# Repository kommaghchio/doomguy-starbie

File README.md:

# README

This project is a modified version of Starbie, the week 1 project for the Half-Life competition. This project includes
all the default features of Starbie, except this time with a rechargable battery and a joystick for additional interactivity.

It also bears the shape of a floppy disk, instead of a star, and has a different pet than the default "Sparkle".

I made this for week 1 on the Half-Life Hack Club competition, using KiCad.

Bill Of Materials (BOM):
|Item                            |Qty|Supplier    |Cost/item|Total Cost|link                                                                                                                                                                                                                                                                                                                                                                                                                                                                                                                                                                                                                                                                                                                                         |
|--------------------------------|---|------------|---------|----------|---------------------------------------------------------------------------------------------------------------------------------------------------------------------------------------------------------------------------------------------------------------------------------------------------------------------------------------------------------------------------------------------------------------------------------------------------------------------------------------------------------------------------------------------------------------------------------------------------------------------------------------------------------------------------------------------------------------------------------------------|
|ESP32-C3                        |1  |Seeed Studio|$4.99    |$4.99     |https://www.seeedstudio.com/Seeed-XIAO-ESP32C3-p-5431.html?gad_source=1&gad_campaignid=12740071602&gclid=CjwKCAjw56zWBhB0EiwAdPOQOaJsaVt_9sGyS2N4amANprfpcpzC4ZFOF3GNRDUXlC3SOKTiNB7X-xoCFh8QAvD_BwE                                                                                                                                                                                                                                                                                                                                                                                                                                                                                                                                         |
|Cherry MX switch                |2  |DigiKey     |$0.95    |$1.90     |https://www.digikey.com/en/products/detail/adafruit-industries-llc/5123/14617350?gclsrc=aw.ds&gad_source=1&gad_campaignid=20243136172&gclid=CjwKCAjw56zWBhB0EiwAdPOQOcEKO_ZuNKcFmKH-LIFbnNIoh5SjWSLckSLV59Q7yF32ZynxiMNdxRoC6DoQAvD_BwE                                                                                                                                                                                                                                                                                                                                                                                                                                                                                                      |
|OLED 128 x 64                   |1  |AliExpress  |$2.25    |$2.25     |https://www.aliexpress.us/item/3256808426200900.html?src=google&src=google&albch=shopping&acnt=708-803-3821&isdl=y&slnk=&plac=&mtctp=&albbt=Google_7_shopping&aff_platform=google&aff_short_key=UneMJZVf&gclsrc=aw.ds&albagn=888888&ds_e_adid=&ds_e_matchtype=&ds_e_device=c&ds_e_network=x&ds_e_product_group_id=&ds_e_product_id=en3256808426200900&ds_e_product_merchant_id=5480922393&ds_e_product_country=US&ds_e_product_language=en&ds_e_product_channel=online&ds_e_product_store_id=&ds_url_v=2&albcp=19558607238&albag=&isSmbAutoCall=false&needSmbHouyi=false&gad_source=4&gad_campaignid=19566915268&gclid=CjwKCAjw56zWBhB0EiwAdPOQOWbCcI1XUyzg5GVxmGdN2MzNH9N6fAxHaXDbBD9-6z0KlFHybVR16RoC3KIQAvD_BwE&gatewayAdapt=glo2usa      |
|DHT 11 Sensor                   |1  |AliExpress  |$2.96    |$2.96     |https://www.aliexpress.us/item/3256808886855570.html?src=google&src=google&albch=shopping&acnt=708-803-3821&isdl=y&slnk=&plac=&mtctp=&albbt=Google_7_shopping&aff_platform=google&aff_short_key=UneMJZVf&gclsrc=aw.ds&albagn=888888&ds_e_adid=&ds_e_matchtype=&ds_e_device=c&ds_e_network=x&ds_e_product_group_id=&ds_e_product_id=en3256808886855570&ds_e_product_merchant_id=689344744&ds_e_product_country=US&ds_e_product_language=en&ds_e_product_channel=online&ds_e_product_store_id=&ds_url_v=2&albcp=19558607238&albag=&isSmbAutoCall=false&needSmbHouyi=false&gad_source=4&gad_campaignid=19566915268&gclid=CjwKCAjw56zWBhB0EiwAdPOQOTi8rHT-l1dalaiymuhlZJ_5rcoiuZagXKZtVVNJyw6yZ1U5YU5x8hoCEt0QAvD_BwE&gatewayAdapt=glo2usa       |
|MPU6050                         |1  |AliExpress  |$1.06    |$1.06     |https://www.aliexpress.us/item/3256811811719256.html?src=google&gatewayAdapt=glo2usa                                                                                                                                                                                                                                                                                                                                                                                                                                                                                                                                                                                                                                                         |
|JST S2B-PH-SM4-TB Male connector|1  |DigiKey     |$0.12    |$0.12     |https://www.digikey.com/en/products/detail/jst-sales-america-inc/S2B-PH-SM4-TB/926655                                                                                                                                                                                                                                                                                                                                                                                                                                                                                                                                                                                                                                                        |
|Li-Po Battery                   |1  |DigiKey     |$7.95    |$7.95     |https://www.digikey.com/en/products/detail/pkcell/LP503035-W-PLUG/26906441?gclsrc=aw.ds&gad_source=1&gad_campaignid=23033451739&gclid=CjwKCAjw56zWBhB0EiwAdPOQOZenrkhbt0bE1SlGZxBGAb4lG4wGcrsO8SRFO7WNs4R7fEYOzQB1sRoCiC4QAvD_BwE                                                                                                                                                                                                                                                                                                                                                                                                                                                                                                            |
|KY-023 joystick                 |1  |AliExpress  |$3.84    |$3.84     |https://www.aliexpress.us/item/3256812405746127.html?src=google&src=google&albch=shopping&acnt=231-612-1468&isdl=y&slnk=&plac=&mtctp=&albbt=Google_7_shopping&aff_platform=google&aff_short_key=_oFgTQeV&gclsrc=aw.ds&albagn=888888&ds_e_adid=&ds_e_matchtype=&ds_e_device=c&ds_e_network=x&ds_e_product_group_id=&ds_e_product_id=en3256812405746127&ds_e_product_merchant_id=5703138139&ds_e_product_country=US&ds_e_product_language=en&ds_e_product_channel=online&ds_e_product_store_id=&ds_url_v=2&albcp=23333650963&albag=&isSmbAutoCall=false&needSmbHouyi=false&gad_source=1&gad_campaignid=23324517798&gclid=CjwKCAjw56zWBhB0EiwAdPOQORNeXun5LSGq2G9BXt7lPJ_d5kZQqLntUko0bx6ymKoTvl06xLSpCxoCtxYQAvD_BwE&gatewayAdapt=glo2usa      |
|Male and Female Pin headers     |1  |AliExpress  |$2.12    |$2.12     |https://www.aliexpress.us/item/2255800687544049.html?src=google&snps=y&src=google&albch=shopping&acnt=708-803-3821&isdl=y&slnk=&plac=&mtctp=&albbt=Google_7_shopping&aff_platform=google&aff_short_key=UneMJZVf&gclsrc=aw.ds&albagn=888888&ds_e_adid=&ds_e_matchtype=&ds_e_device=c&ds_e_network=x&ds_e_product_group_id=&ds_e_product_id=en2255800687544049&ds_e_product_merchant_id=107851422&ds_e_product_country=US&ds_e_product_language=en&ds_e_product_channel=online&ds_e_product_store_id=&ds_url_v=2&albcp=20542171667&albag=&isSmbAutoCall=false&needSmbHouyi=false&gad_source=1&gad_campaignid=18545443176&gclid=CjwKCAjw56zWBhB0EiwAdPOQOXWeQ7sWc4y_nkJD0D0cMJH5K3kBbSc2pA1cyd5qMiuMDiqWgesMORoCqAYQAvD_BwE&gatewayAdapt=glo2usa|
|PCB                             |1  |JLCPCB      |$8.99    |$8.99     |https://jlcpcb.com                                                                                                                                                                                                                                                                                                                                                                                                                                                                                                                                                                                                                                                                                                                           |
|Estimated total shipping        |1  |            |         |$0.00     |                                                                                                                                                                                                                                                                                                                                                                                                                                                                                                                                                                                                                                                                                                                                             |

Assembly:
Firstly, get the ESP32 in place, on the bottom-right of the board, there are pads and traces just fit for it! use those exact pads and traces, and orient the ESP32 in a way so that it's facing to the outside of the board, not inside. on J4, solder the JST connector to the board, so that positive is on the right, next, on R1, solder the resistor so that the positive input goes to 3.3v. Next to it is where the DHT 11 sensor will go, the square hole is where positive 3.3V will go. Just above is J2, where the MPU6050 will go, once again, the square hole is where 3.3 is on the sensor. Above that, towards the top is the 2 switches, solder those 2 as well, it's impossible to mess this up unless you're soldering to the backside, which you shouldn't be anyway. Finally is the joystick, where once again the square pin is used for alignment, but instead that's where ground goes. Smack dab in the middle is the OLED, where once again you have to just not be an idiot.

Before you can turn it on, you must flash the ESP-32, download the .ino file and plug the ESP32 in, then just flash it with the Arduino software like any other board, make sure the settings are correct though.

doomguy-starbie render:

schematic:

pcb:

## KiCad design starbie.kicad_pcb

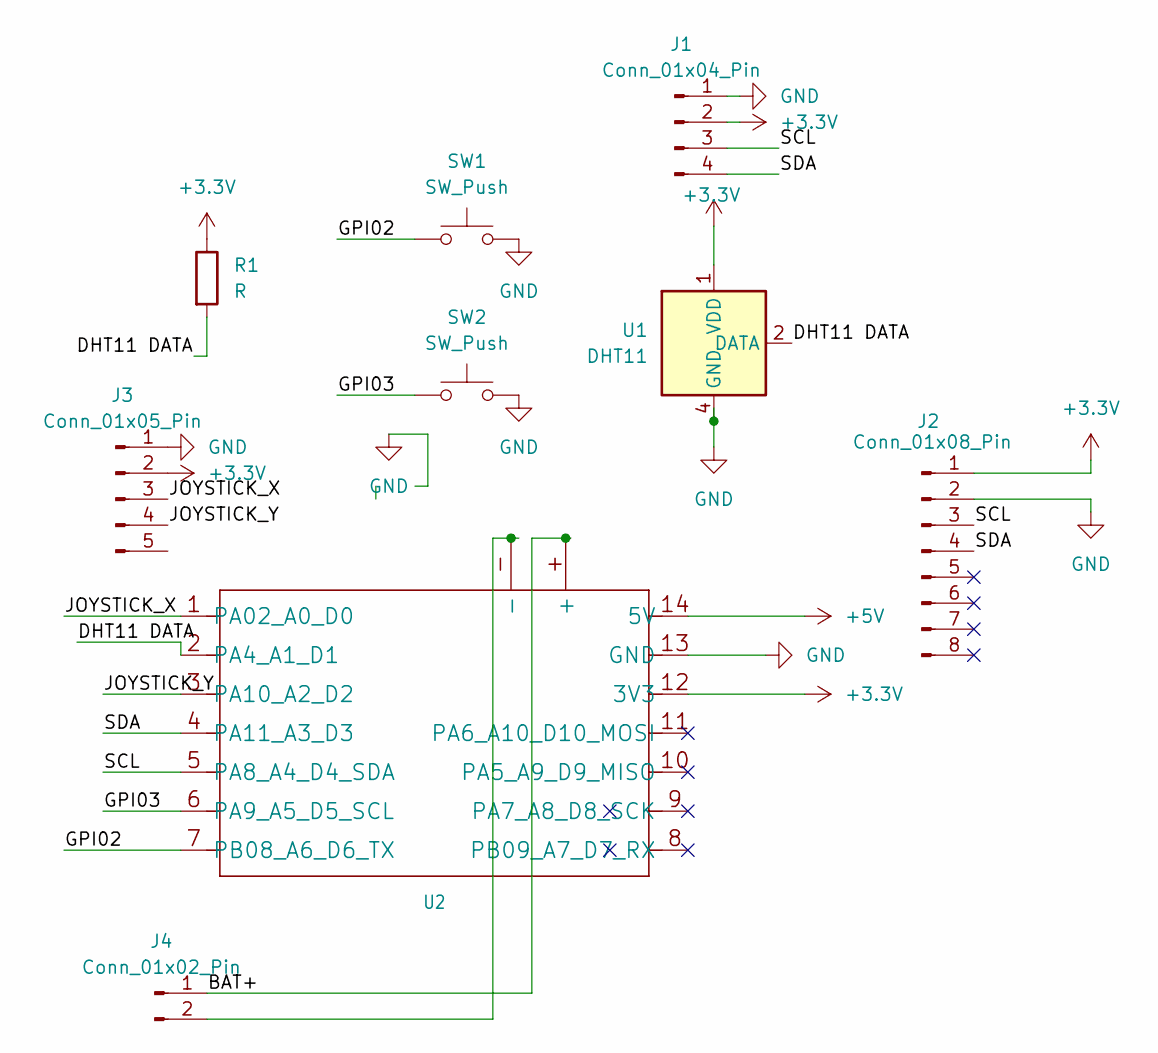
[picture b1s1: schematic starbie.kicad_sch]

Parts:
J1: Conn_01x04_Pin; Display_128x64_096_I2C
J2: Conn_01x08_Pin; PinHeader_1x08_P2.54mm_Vertical
J3: Conn_01x05_Pin; PinSocket_1x05_P2.54mm_Vertical
J4: Conn_01x02_Pin; JST_PH_S2B-PH-SM4-TB_1x02-1MP_P2.00mm_Horizontal
R1: R; R_Axial_DIN0204_L3.6mm_D1.6mm_P7.62mm_Horizontal
SW1, SW2: SW_Push; SW_Cherry_MX_1.00u_PCB
U1: DHT11; Aosong_DHT11_5.5x12.0_P2.54mm
U2: MOUDLE14P-SMD-2.54-21X17.8MM

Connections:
+3.3V: J1.2, J2.1, J3.2, R1.1, U1.1 (VDD), U2.12 (3V3)
+5V: U2.14 (5V)
/BAT+: J4.1, U2.+
/DHT11 DATA: R1.2, U1.2 (DATA), U2.2 (PA4_A1_D1)
/GPI02: SW1.1, U2.7 (PB08_A6_D6_TX)
/GPI03: SW2.1, U2.6 (PA9_A5_D5_SCL)
/JOYSTICK_X: J3.3, U2.1 (PA02_A0_D0)
/JOYSTICK_Y: J3.4, U2.3 (PA10_A2_D2)
/SCL: J1.3, J2.3, U2.5 (PA8_A4_D4_SDA)
/SDA: J1.4, J2.4, U2.4 (PA11_A3_D3)
GND: J1.1, J2.2, J3.1, SW1.2, SW2.2, U1.4 (GND), U2.13 (GND)
unnamed: J4.2, U2.-

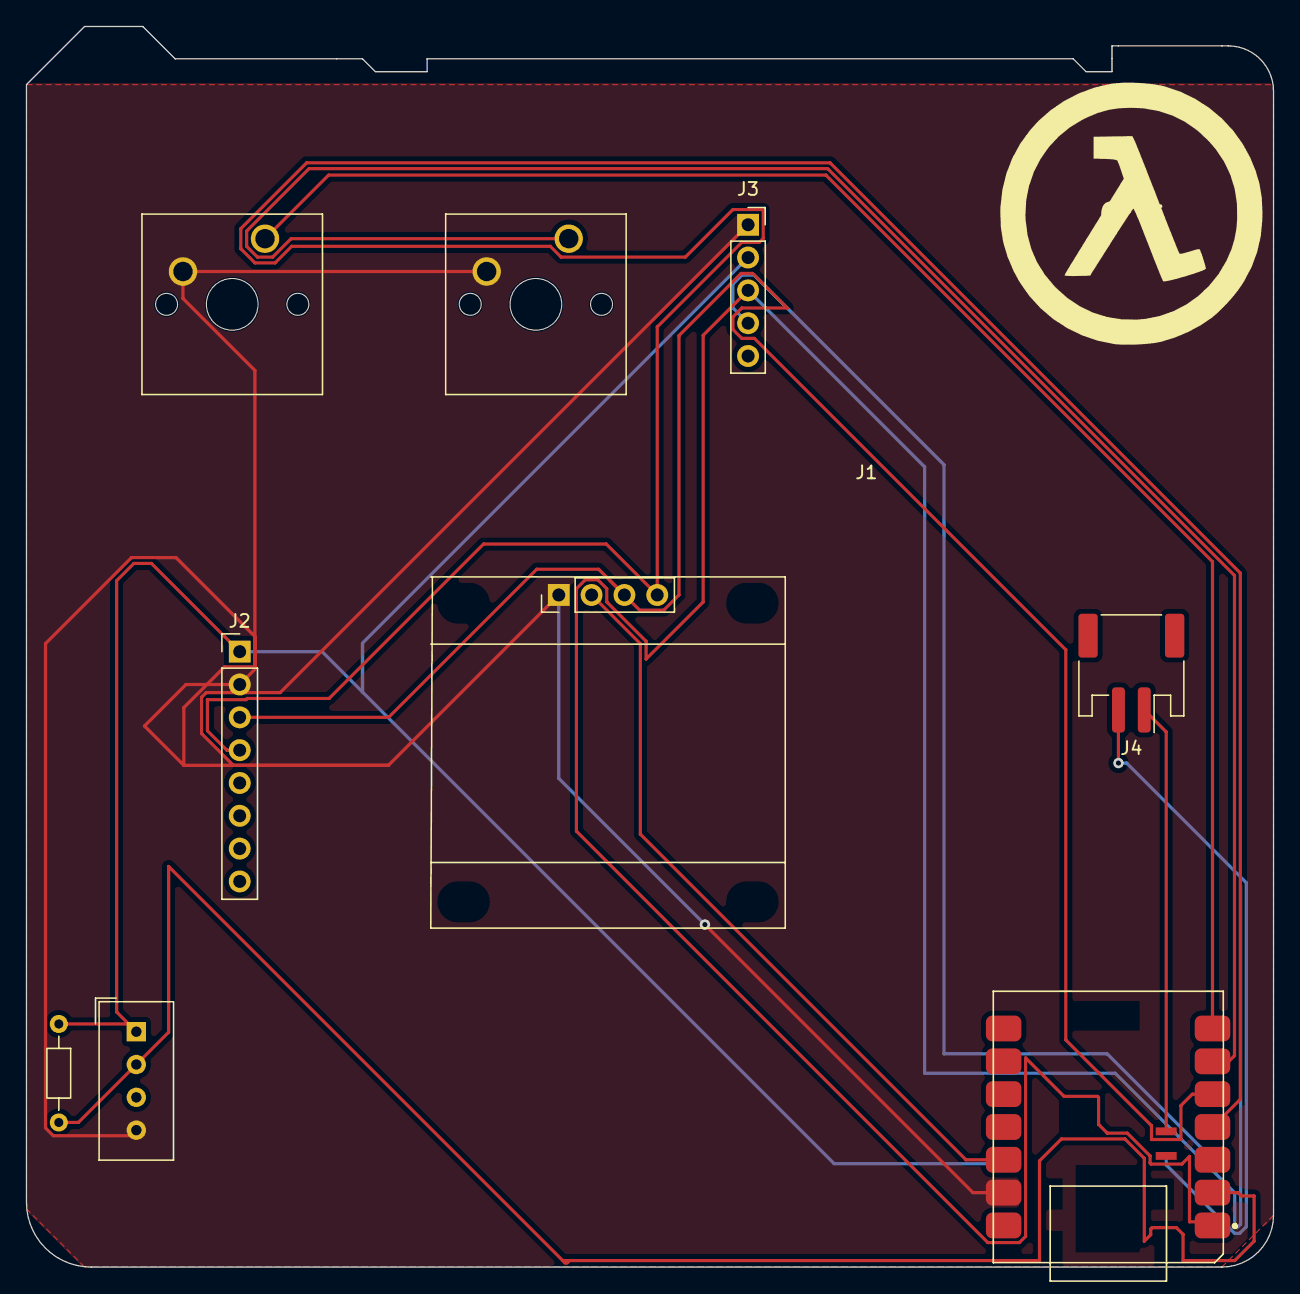
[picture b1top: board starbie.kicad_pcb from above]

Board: 2 copper layers, 96.5 x 96.0 mm, 9 parts (0 on the bottom side), 11 nets.
